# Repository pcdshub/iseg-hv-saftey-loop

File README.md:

# iseg-hv-saftey-loop

PCB-based design for iseg HV power supply safety loop with filtering capacitors and bypass switches.

EDA software: KiCAD 7.0

# screenshot

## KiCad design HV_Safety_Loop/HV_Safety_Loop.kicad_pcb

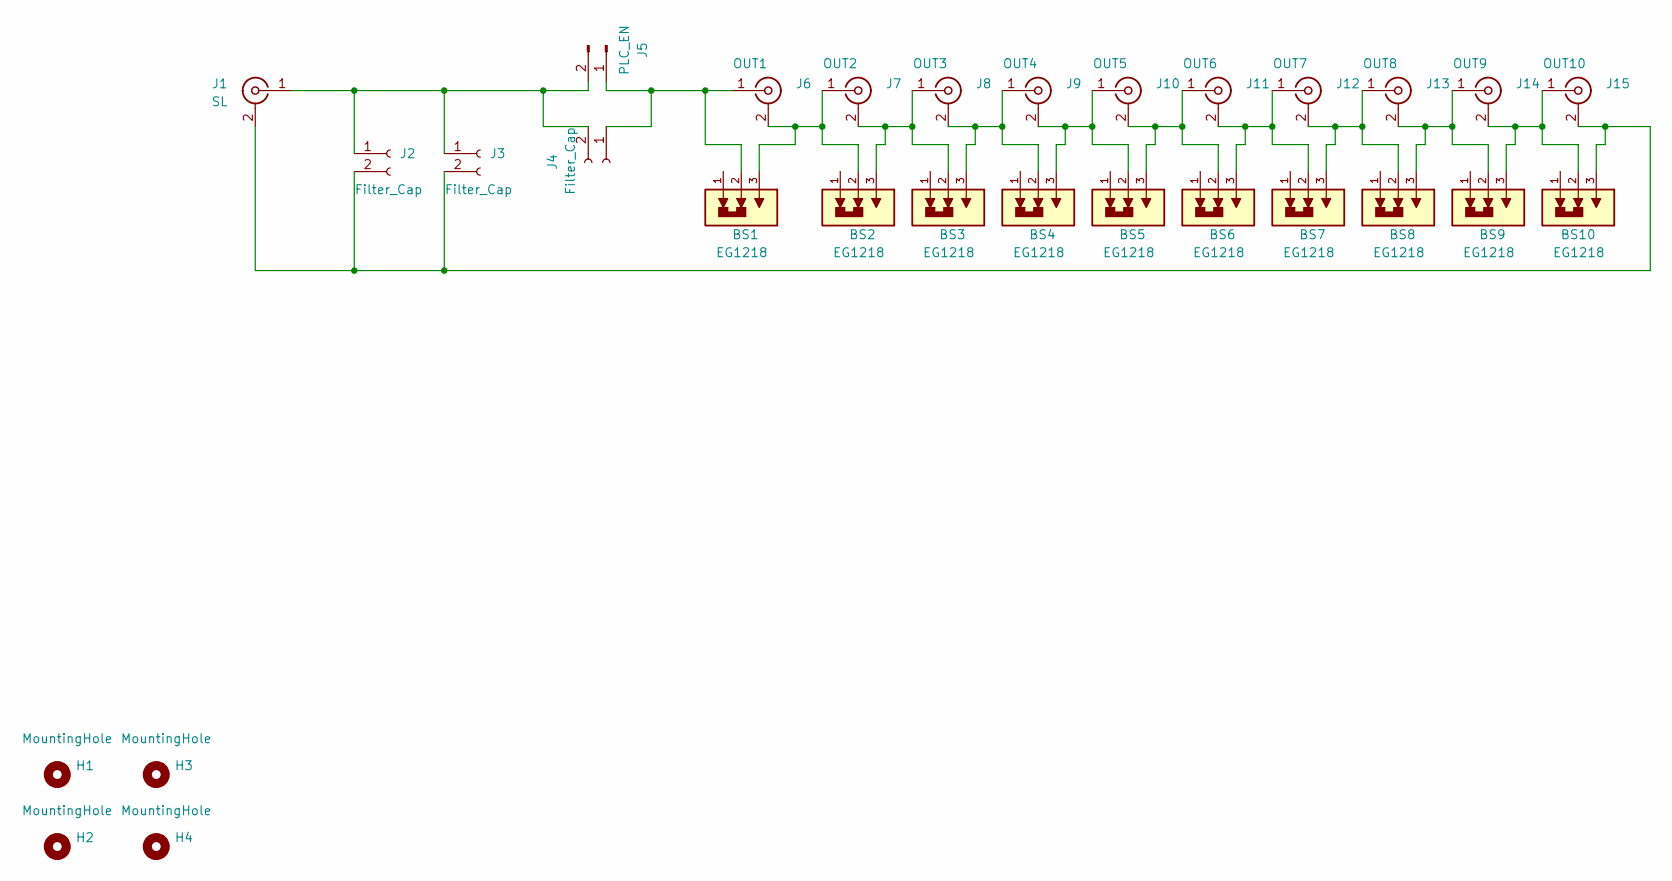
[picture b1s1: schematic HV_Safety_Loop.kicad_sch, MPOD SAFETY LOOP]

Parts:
BS1, BS2, BS3, BS4, BS5, BS6, BS7, BS8, BS9, BS10: EG1218; SW_EG1218
H1, H3: MountingHole; MountingHole_2.7mm_M2.5_DIN965_Pad
H2, H4: MountingHole; MountingHole_2.2mm_M2_DIN965_Pad
J1: SL; SMB_Jack_Vertical
J2, J3, J4: Filter_Cap; PinSocket_1x02_P2.54mm_Vertical
J5: PLC_EN; PhoenixContact_MSTBA_2,5_2-G-5,08_1x02_P5.08mm_Horizontal
J6: OUT1; SMB_Jack_Vertical
J7: OUT2; SMB_Jack_Vertical
J8: OUT3; SMB_Jack_Vertical
J9: OUT4; SMB_Jack_Vertical
J10: OUT5; SMB_Jack_Vertical
J11: OUT6; SMB_Jack_Vertical
J12: OUT7; SMB_Jack_Vertical
J13: OUT8; SMB_Jack_Vertical
J14: OUT9; SMB_Jack_Vertical
J15: OUT10; SMB_Jack_Vertical

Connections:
unnamed: BS10.3, J1.2 (Ext), J2.2, J3.2, J15.2 (Ext)
unnamed: J1.1 (In), J2.1, J3.1, J4.2, J5.2
unnamed: BS1.2, J4.1, J5.1, J6.1 (In)
unnamed: BS1.3, BS2.2, J6.2 (Ext), J7.1 (In)
unnamed: BS2.3, BS3.2, J7.2 (Ext), J8.1 (In)
unnamed: BS3.3, BS4.2, J8.2 (Ext), J9.1 (In)
unnamed: BS5.3, BS6.2, J10.2 (Ext), J11.1 (In)
unnamed: BS4.3, BS5.2, J9.2 (Ext), J10.1 (In)
unnamed: BS6.3, BS7.2, J11.2 (Ext), J12.1 (In)
unnamed: BS7.3, BS8.2, J12.2 (Ext), J13.1 (In)
unnamed: BS8.3, BS9.2, J13.2 (Ext), J14.1 (In)
unnamed: BS9.3, BS10.2, J14.2 (Ext), J15.1 (In)

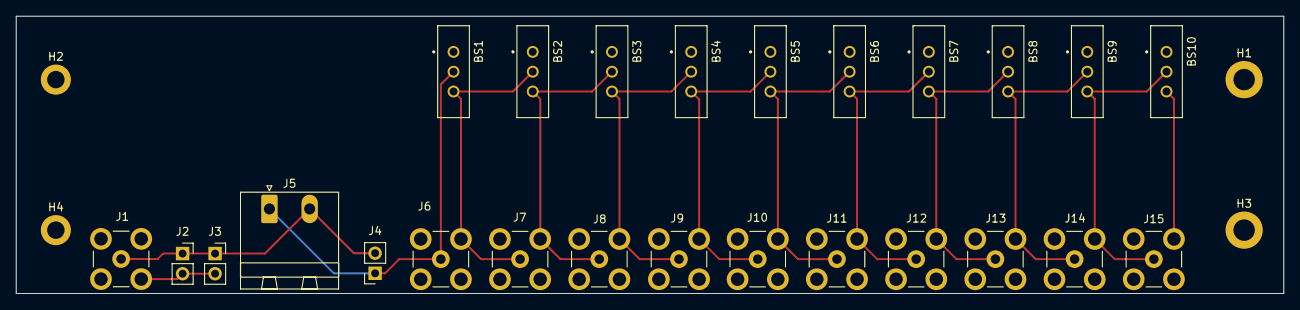
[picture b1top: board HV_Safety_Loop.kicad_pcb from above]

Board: 2 copper layers, 160.0 x 35.0 mm, 29 parts (0 on the bottom side), 12 nets.

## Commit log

2023-11-10 init commit
2023-11-10 update screenshot image
2023-11-11 change bypass switch to E1218, add bypass capacitor for plc connector
2023-11-14 fix pcb layout
2025-04-15 MNT: Adding CODEOWNERS file
